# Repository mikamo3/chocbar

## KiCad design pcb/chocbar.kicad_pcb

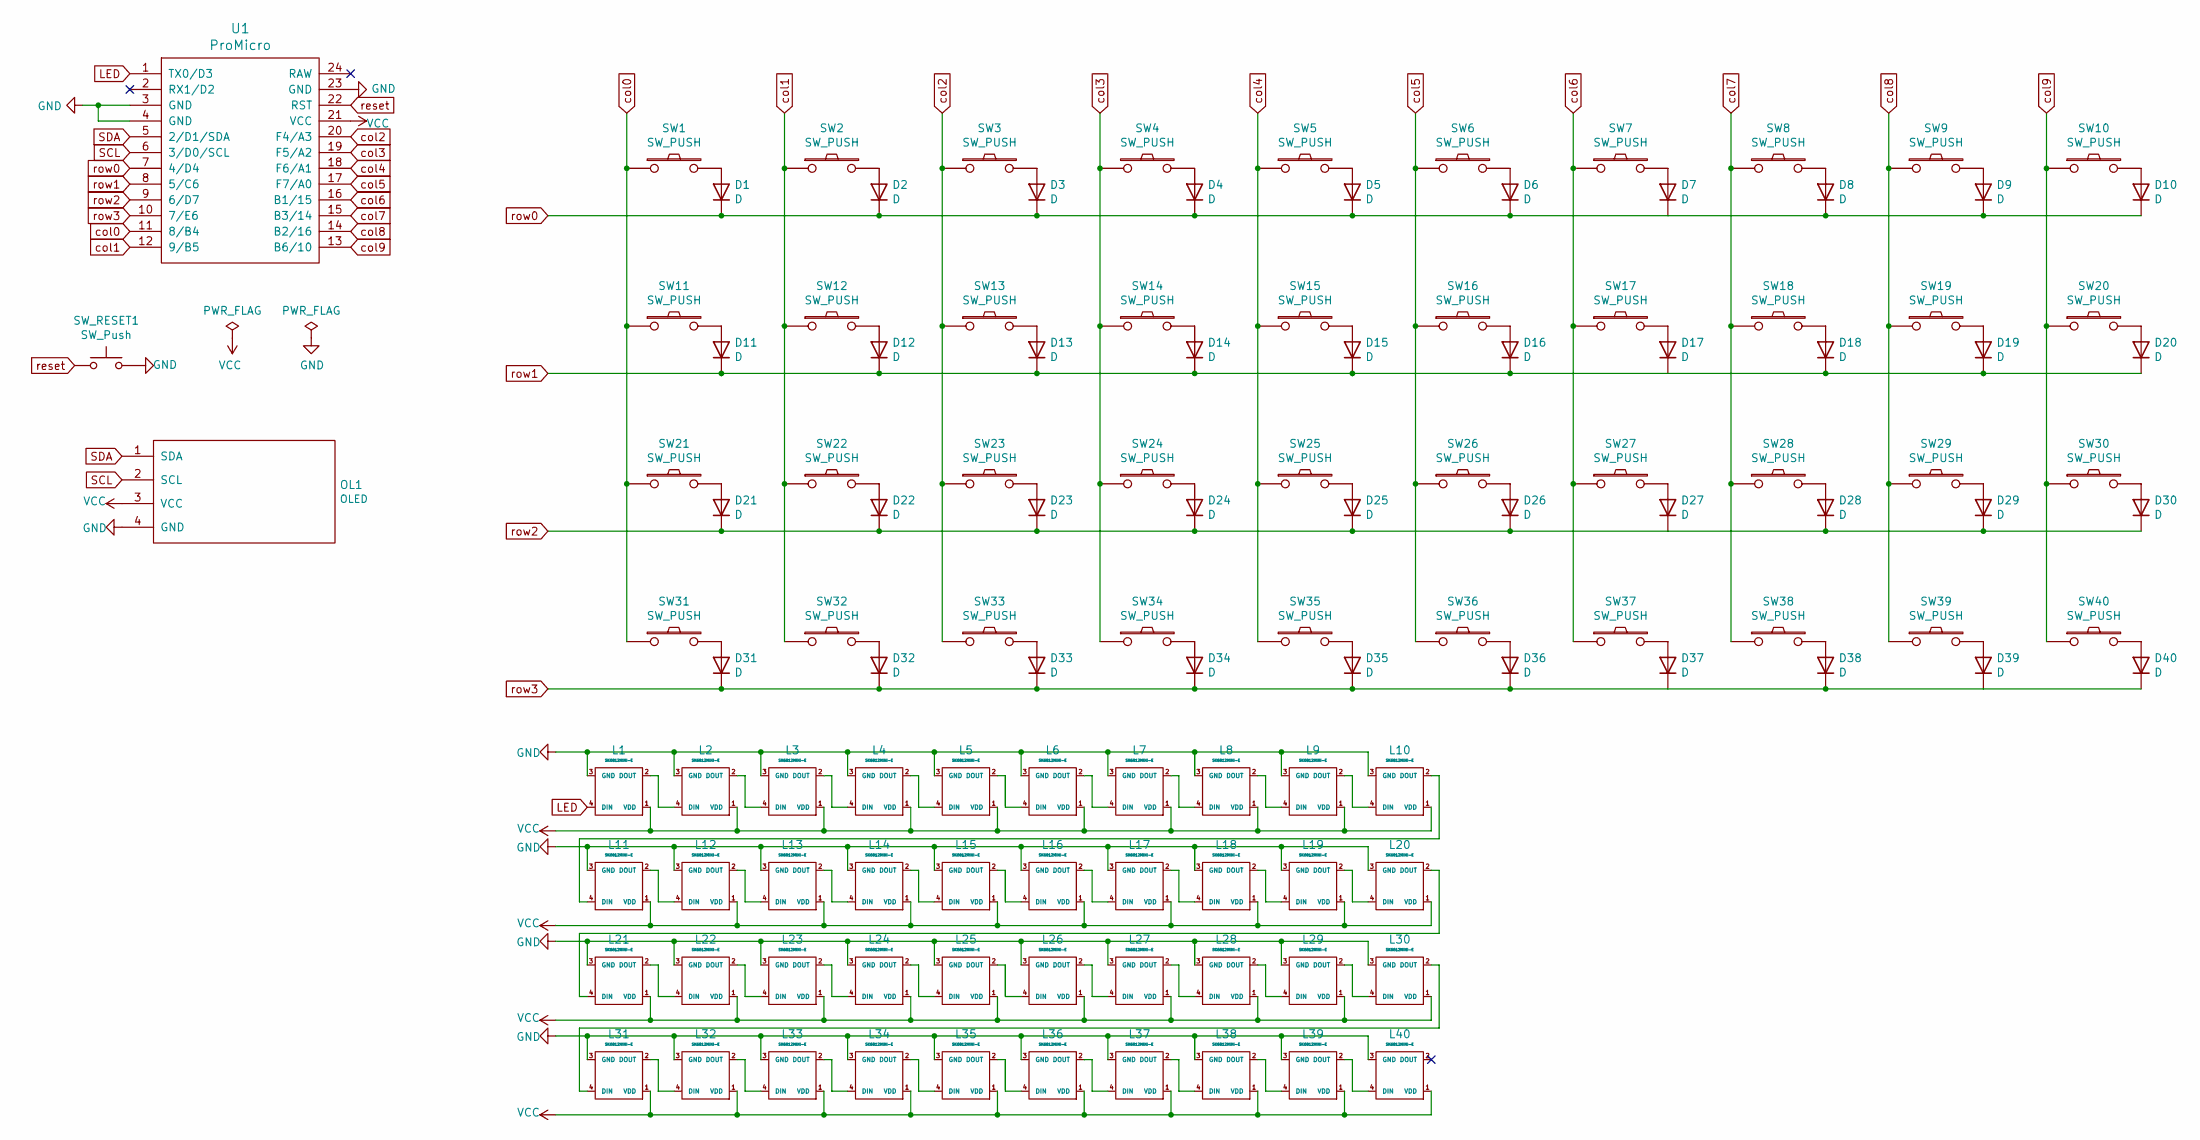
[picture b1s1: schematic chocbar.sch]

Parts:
D1, D2, D3, D4, D5, D6, D7, D8, D9, D10, D11, D12, D13, D14, D15, D16, D17, D18, D19, D20, D21, D22, D23, D24, D25, D26, D27, D28, D29, D30, D31, D32, D33, D34, D35, D36, D37, D38, D39, D40: D; D3_SMD_1side
L1, L2, L3, L4, L5, L6, L7, L8, L9, L10, L11, L12, L13, L14, L15, L16, L17, L18, L19, L20, L21, L22, L23, L24, L25, L26, L27, L28, L29, L30, L31, L32, L33, L34, L35, L36, L37, L38, L39, L40: SK6812MINI-E; YS-SK6812MINI-E
OL1: OLED; OLED_1side
SW1, SW2, SW3, SW4, SW5, SW6, SW7, SW8, SW9, SW10, SW11, SW12, SW13, SW14, SW15, SW16, SW17, SW18, SW19, SW20, SW21, SW22, SW23, SW24, SW25, SW26, SW27, SW28, SW29, SW30, SW31, SW32, SW37, SW38, SW39, SW40: SW_PUSH; Choc_Hotswap_1side
SW33, SW34, SW35, SW36: SW_PUSH; Choc_Hotswap_1.5u_1side
SW_RESET1: SW_Push; ResetSW_1side
U1: ProMicro; ProMicro_v3.5

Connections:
GND: L1.3 (GND), L2.3 (GND), L3.3 (GND), L4.3 (GND), L5.3 (GND), L6.3 (GND), L7.3 (GND), L8.3 (GND), L9.3 (GND), L10.3 (GND), L11.3 (GND), L12.3 (GND), L13.3 (GND), L14.3 (GND), L15.3 (GND), L16.3 (GND), L17.3 (GND), L18.3 (GND), L19.3 (GND), L20.3 (GND), L21.3 (GND), L22.3 (GND), L23.3 (GND), L24.3 (GND), L25.3 (GND), L26.3 (GND), L27.3 (GND), L28.3 (GND), L29.3 (GND), L30.3 (GND), L31.3 (GND), L32.3 (GND), L33.3 (GND), L34.3 (GND), L35.3 (GND), L36.3 (GND), L37.3 (GND), L38.3 (GND), L39.3 (GND), L40.3 (GND), OL1.4 (GND), SW_RESET1.2, U1.3 (GND), U1.4 (GND), U1.23 (GND)
LED: L1.4 (DIN), U1.1 (TX0/D3)
unnamed: D1.2 (A), SW1.2
unnamed: D2.2 (A), SW2.2
unnamed: D3.2 (A), SW3.2
unnamed: D4.2 (A), SW4.2
unnamed: D5.2 (A), SW5.2
unnamed: D6.2 (A), SW6.2
unnamed: D7.2 (A), SW7.2
unnamed: D8.2 (A), SW8.2
unnamed: D9.2 (A), SW9.2
unnamed: D10.2 (A), SW10.2
unnamed: D11.2 (A), SW11.2
unnamed: D12.2 (A), SW12.2
unnamed: D13.2 (A), SW13.2
unnamed: D14.2 (A), SW14.2
unnamed: D15.2 (A), SW15.2
unnamed: D16.2 (A), SW16.2
unnamed: D17.2 (A), SW17.2
unnamed: D18.2 (A), SW18.2
unnamed: D19.2 (A), SW19.2
unnamed: D20.2 (A), SW20.2
unnamed: D21.2 (A), SW21.2
unnamed: D22.2 (A), SW22.2
unnamed: D23.2 (A), SW23.2
unnamed: D24.2 (A), SW24.2
unnamed: D25.2 (A), SW25.2
unnamed: D26.2 (A), SW26.2
unnamed: D27.2 (A), SW27.2
unnamed: D28.2 (A), SW28.2
unnamed: D29.2 (A), SW29.2
unnamed: D30.2 (A), SW30.2
unnamed: D31.2 (A), SW31.2
unnamed: D32.2 (A), SW32.2
unnamed: D33.2 (A), SW33.2
unnamed: D34.2 (A), SW34.2
unnamed: D35.2 (A), SW35.2
unnamed: D36.2 (A), SW36.2
unnamed: D37.2 (A), SW37.2
unnamed: D38.2 (A), SW38.2
unnamed: D39.2 (A), SW39.2
unnamed: D40.2 (A), SW40.2
unnamed: L1.2 (DOUT), L2.4 (DIN)
unnamed: L2.2 (DOUT), L3.4 (DIN)
unnamed: L3.2 (DOUT), L4.4 (DIN)
unnamed: L4.2 (DOUT), L5.4 (DIN)
unnamed: L5.2 (DOUT), L6.4 (DIN)
unnamed: L6.2 (DOUT), L7.4 (DIN)
unnamed: L7.2 (DOUT), L8.4 (DIN)
unnamed: L8.2 (DOUT), L9.4 (DIN)
unnamed: L10.2 (DOUT), L11.4 (DIN)
unnamed: L9.2 (DOUT), L10.4 (DIN)
unnamed: L11.2 (DOUT), L12.4 (DIN)
unnamed: L12.2 (DOUT), L13.4 (DIN)
unnamed: L13.2 (DOUT), L14.4 (DIN)
unnamed: L14.2 (DOUT), L15.4 (DIN)
unnamed: L15.2 (DOUT), L16.4 (DIN)
unnamed: L16.2 (DOUT), L17.4 (DIN)
unnamed: L17.2 (DOUT), L18.4 (DIN)
unnamed: L18.2 (DOUT), L19.4 (DIN)
unnamed: L19.2 (DOUT), L20.4 (DIN)
unnamed: L20.2 (DOUT), L21.4 (DIN)
unnamed: L21.2 (DOUT), L22.4 (DIN)
unnamed: L22.2 (DOUT), L23.4 (DIN)
unnamed: L23.2 (DOUT), L24.4 (DIN)
unnamed: L24.2 (DOUT), L25.4 (DIN)
unnamed: L25.2 (DOUT), L26.4 (DIN)
unnamed: L26.2 (DOUT), L27.4 (DIN)
unnamed: L27.2 (DOUT), L28.4 (DIN)
unnamed: L28.2 (DOUT), L29.4 (DIN)
unnamed: L29.2 (DOUT), L30.4 (DIN)
unnamed: L30.2 (DOUT), L31.4 (DIN)
unnamed: L31.2 (DOUT), L32.4 (DIN)
unnamed: L32.2 (DOUT), L33.4 (DIN)
unnamed: L33.2 (DOUT), L34.4 (DIN)
unnamed: L34.2 (DOUT), L35.4 (DIN)
unnamed: L35.2 (DOUT), L36.4 (DIN)
unnamed: L36.2 (DOUT), L37.4 (DIN)
unnamed: L37.2 (DOUT), L38.4 (DIN)
unnamed: L38.2 (DOUT), L39.4 (DIN)
unnamed: L39.2 (DOUT), L40.4 (DIN)
SCL: OL1.2 (SCL), U1.6 (3/D0/SCL)
SDA: OL1.1 (SDA), U1.5 (2/D1/SDA)
VCC: L1.1 (VDD), L2.1 (VDD), L3.1 (VDD), L4.1 (VDD), L5.1 (VDD), L6.1 (VDD), L7.1 (VDD), L8.1 (VDD), L9.1 (VDD), L10.1 (VDD), L11.1 (VDD), L12.1 (VDD), L13.1 (VDD), L14.1 (VDD), L15.1 (VDD), L16.1 (VDD), L17.1 (VDD), L18.1 (VDD), L19.1 (VDD), L20.1 (VDD), L21.1 (VDD), L22.1 (VDD), L23.1 (VDD), L24.1 (VDD), L25.1 (VDD), L26.1 (VDD), L27.1 (VDD), L28.1 (VDD), L29.1 (VDD), L30.1 (VDD), L31.1 (VDD), L32.1 (VDD), L33.1 (VDD), L34.1 (VDD), L35.1 (VDD), L36.1 (VDD), L37.1 (VDD), L38.1 (VDD), L39.1 (VDD), L40.1 (VDD), OL1.3 (VCC), U1.21 (VCC)
col0: SW1.1, SW11.1, SW21.1, SW31.1, U1.11 (8/B4)
col1: SW2.1, SW12.1, SW22.1, SW32.1, U1.12 (9/B5)
col2: SW3.1, SW13.1, SW23.1, SW33.1, U1.20 (F4/A3)
col3: SW4.1, SW14.1, SW24.1, SW34.1, U1.19 (F5/A2)
col4: SW5.1, SW15.1, SW25.1, SW35.1, U1.18 (F6/A1)
col5: SW6.1, SW16.1, SW26.1, SW36.1, U1.17 (F7/A0)
col6: SW7.1, SW17.1, SW27.1, SW37.1, U1.16 (B1/15)
col7: SW8.1, SW18.1, SW28.1, SW38.1, U1.15 (B3/14)
col8: SW9.1, SW19.1, SW29.1, SW39.1, U1.14 (B2/16)
col9: SW10.1, SW20.1, SW30.1, SW40.1, U1.13 (B6/10)
reset: SW_RESET1.1, U1.22 (RST)
row0: D1.1 (K), D2.1 (K), D3.1 (K), D4.1 (K), D5.1 (K), D6.1 (K), D7.1 (K), D8.1 (K), D9.1 (K), D10.1 (K), U1.7 (4/D4)
row1: D11.1 (K), D12.1 (K), D13.1 (K), D14.1 (K), D15.1 (K), D16.1 (K), D17.1 (K), D18.1 (K), D19.1 (K), D20.1 (K), U1.8 (5/C6)
row2: D21.1 (K), D22.1 (K), D23.1 (K), D24.1 (K), D25.1 (K), D26.1 (K), D27.1 (K), D28.1 (K), D29.1 (K), D30.1 (K), U1.9 (6/D7)
row3: D31.1 (K), D32.1 (K), D33.1 (K), D34.1 (K), D35.1 (K), D36.1 (K), D37.1 (K), D38.1 (K), D39.1 (K), D40.1 (K), U1.10 (7/E6)

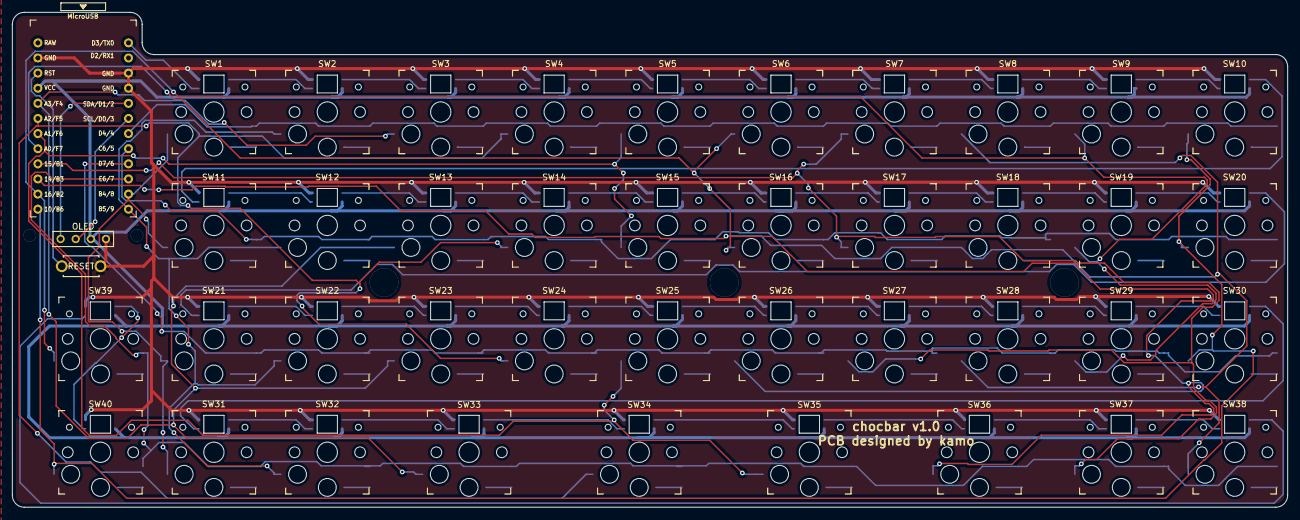
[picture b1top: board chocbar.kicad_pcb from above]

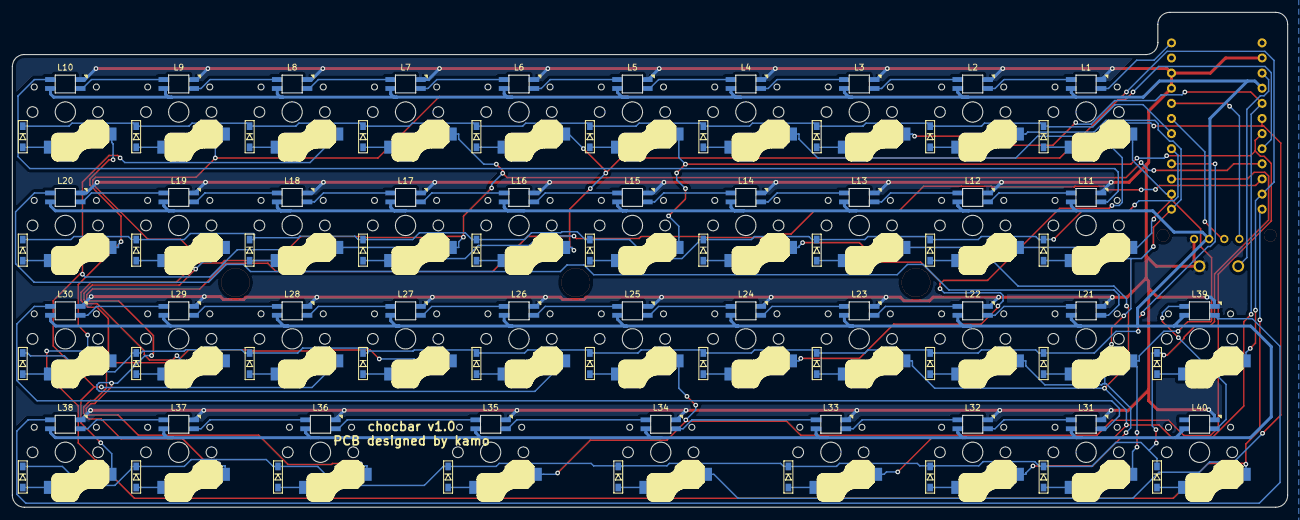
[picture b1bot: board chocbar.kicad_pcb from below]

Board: 2 copper layers, 214.2 x 83.1 mm, 128 parts (80 on the bottom side), 99 nets.

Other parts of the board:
H1, H2, H3, H4, H5: Val**; M2_HOLE_v2

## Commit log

2020-07-14 firstcommit
2020-07-20 add pcb and plate
2020-08-09 improve
2020-11-07 fix pcb and plate
2020-12-06 :heavy_plus_sign: (lib) fix submodule
2023-06-17 :sparkles: (all) add
